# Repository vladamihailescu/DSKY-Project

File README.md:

# DSKY-Project
My open source journey to building a functional, historically-accurate DSKY interface that can be used in simulation. 
 
## v1.0 Hardware (Completed)
 - Raspberry Pi 3B+ running VirtualAGC + driving the display & keyboard
 - Nextion 4.3" LCD HMI (NX4827T043_11) display
 - Alarm Panel PCB designed by Riley Rainey
 - Hand assembled keyboard using Cherry MX blue key switches & Arduino UNO in USB HID mode
 - 3D Printed shell components made from models created/modified by Riley Rainey/Manoel DaSilva from original MIT drawings or myself

## v1.5 Hardware (In Progress)
 - Raspberry Pi 3B+ running VirtualAGC + driving the display & keyboard
 - Nextion 4.3" LCD HMI (NX4827T043_11) display
 - Alarm Panel PCB designed by Riley Rainey
 - Keyboard PCB designed by me with Cherry MX green key switches & LED backlighting
 - 3D Printed shell components made from models created/modified by Riley Rainey/Manoel DaSilva from original MIT drawings or myself

## v2.0 Hardware (Planned)
 - Raspberry Pi 3B+ running VirtualAGC + driving the display & keyboard
 - Custom EL display panel
 - Alarm Panel PCB designed by Riley Rainey
 - Keyboard switches assembled as per original spec using microswitches
 - 3D Printed shell components made from models created/modified by Riley Rainey from original MIT drawings or myself

## Software
 - Drivers for display, alarm panel & keyboard written in Python3
 - VirtualAGC project
 - Project Apollo - NASSP
 
## Setup
Raspberry Pi running VirtualAGC is driving the Nextion HMI, sending lamp instructions to the Alert board and reading keystrokes from Keyboard

## Task List
- 1.0
- [x] Build working GUI for HMI display
- [x] Driver for Nextion HMI display
- [x] Assemble alarm panel PCB
- [x] Driver for alarm panel
- [x] Assemble keyboard
- [x] Driver for keyboard
- [x] Update piDSKY2.py file
- [x] Test with VirtualAGC

- 1.5
- [x] Design & assemble a custom PCB for keyboard
- [ ] Improve code
- [ ] Refine GUI to more closely match original DSKY display
- [ ] Keyboard caps improvements
- [ ] Improve overall DSKY fit & finish & pave way to v2.0

## References
 [VirtualAGC Project](https://www.ibiblio.org/apollo/) - I am so thankful that this exists because it has been my dream to build my own DSKY ever since I first learned of the
 project\
 [Riley Rainey](https://github.com/rrainey) - His amazing work in designing the alert and keyboard PCBs, modeling the DSKY shell and inner components from original drawings gave
 me the opportunity to start this project\
 [Manoel DaSilva](https://github.com/ManoDaSilva) - He created the HMI file which I modified and adapted to my code and the Cherry MX keyswitch stems I used.\

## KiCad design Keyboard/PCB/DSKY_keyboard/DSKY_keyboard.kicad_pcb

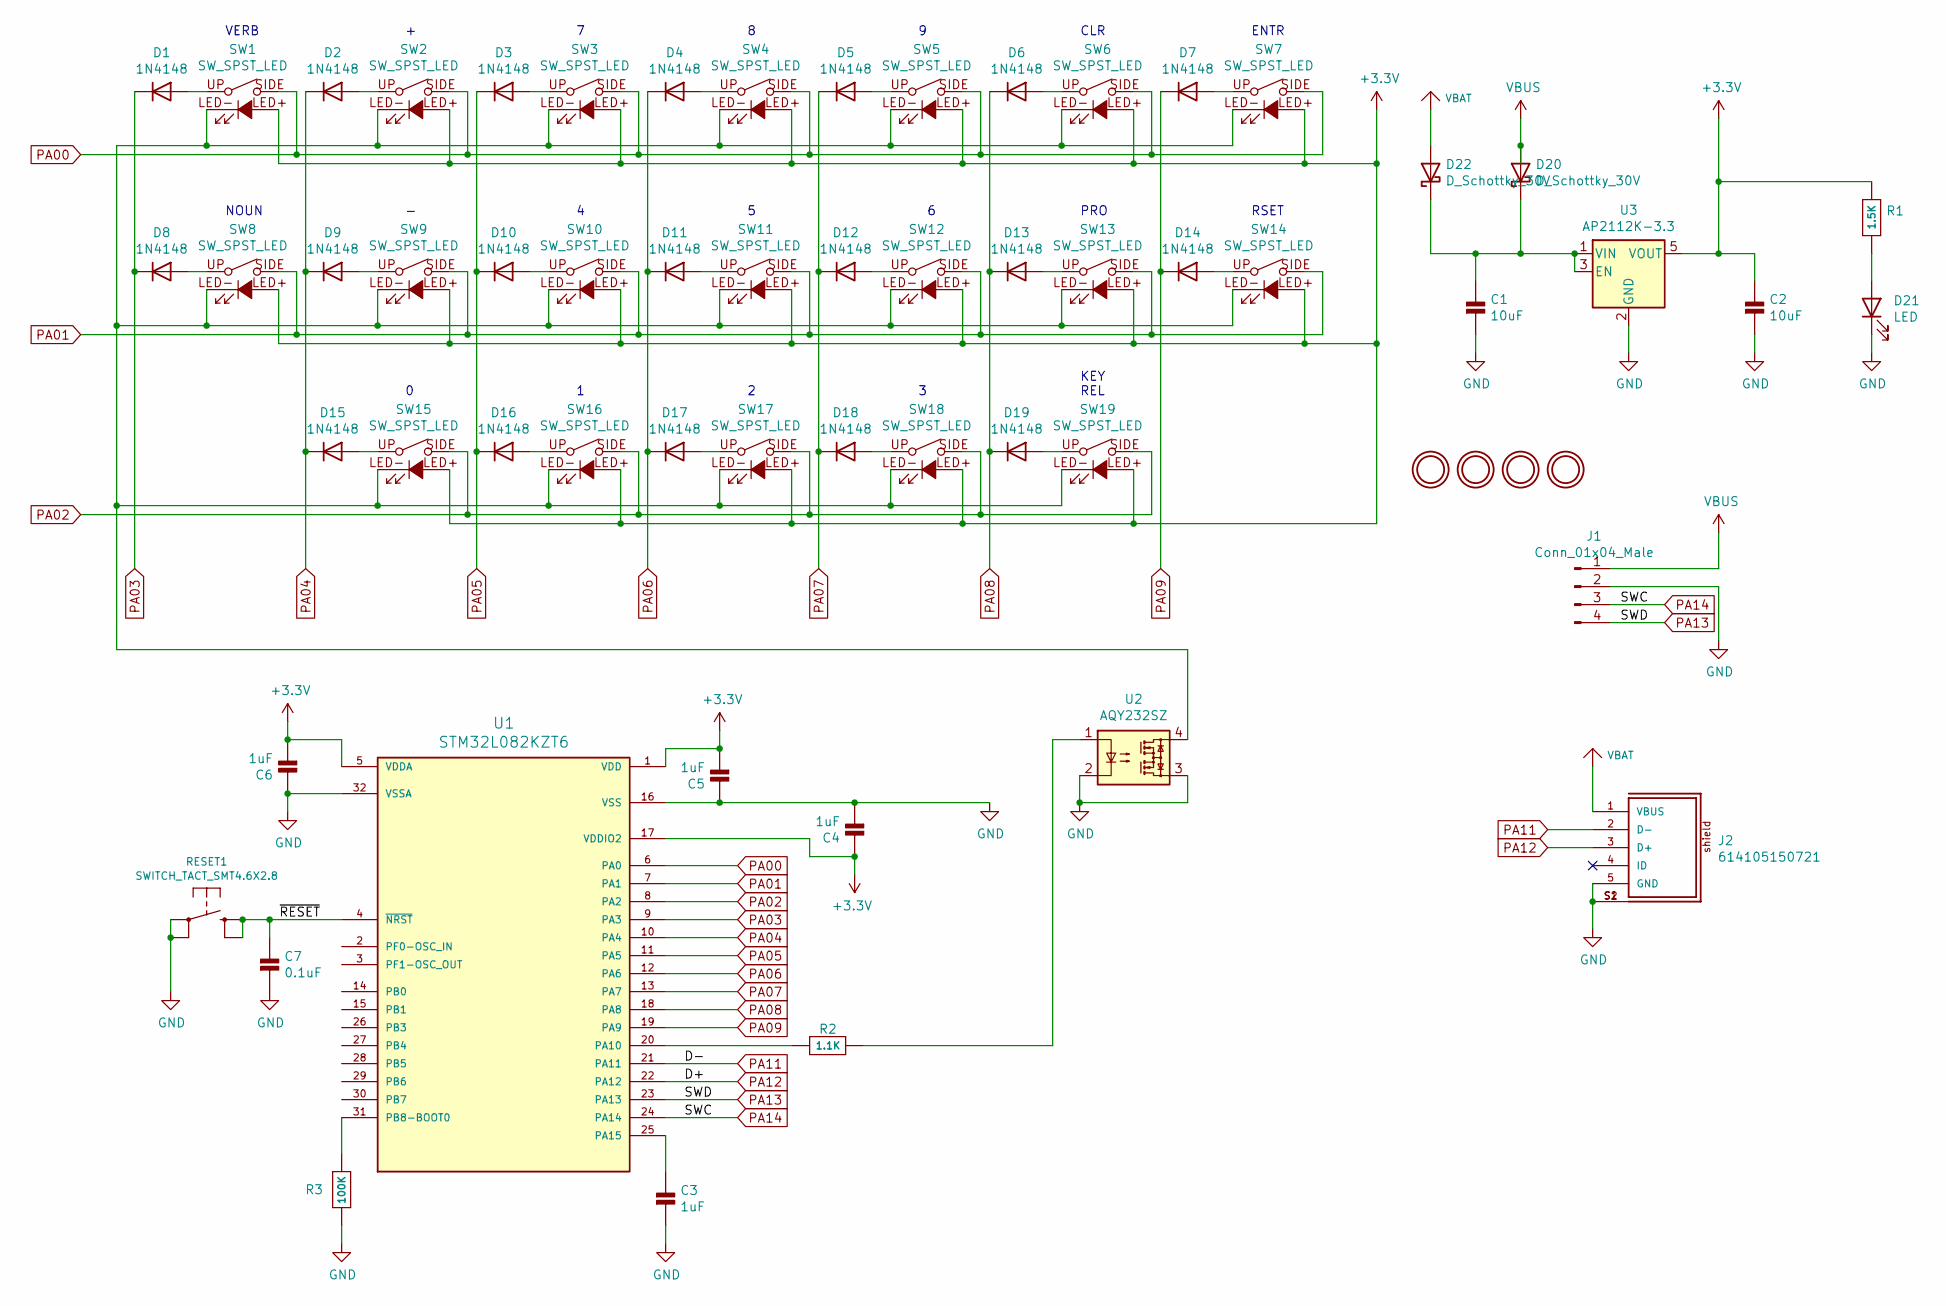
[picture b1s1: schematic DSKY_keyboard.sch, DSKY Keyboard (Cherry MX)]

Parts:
C1, C2: 10uF; 0805-NO
C3, C4, C5, C6: 1uF; 0603-NO
C7: 0.1uF; 0603-NO
D1, D2, D3, D4, D5, D6, D7, D8, D9, D10, D11, D12, D13, D14, D15, D16, D17, D18, D19: 1N4148; SOD-123
D20, D22: D_Schottky_30V; SOD-123FL
D21: LED; CHIPLED_0603_NOOUTLINE
J1: Conn_01x04_Male; PinHeader_1x04_P2.54mm_Horizontal
J2: 614105150721; PART-NUMBER 614105150721
J3, J4, J5, J6: MOUNTINGHOLE3.0; MOUNTINGHOLE_2.0_PLATED
R1: 1.5K; 0603-NO
R2: 1.1K; 0603-NO
R3: 100K; 0603-NO
RESET1: SWITCH_TACT_SMT4.6X2.8; BTN_KMR2_4.6X2.8
SW1, SW2, SW3, SW4, SW5, SW6, SW7, SW8, SW9, SW10, SW11, SW12, SW13, SW14, SW15, SW16, SW17, SW18, SW19: SW_SPST_LED; CHERRYMX-NN-LED
U1: STM32L082KZT6; STM32F042K6T6
U2: AQY232SZ; SO-4_4.4x4.3mm_P2.54mm
U3: AP2112K-3.3; SOT23-5

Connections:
+3V3: C2.1, C4.1, C5.2, C6.2, R1.1, SW1.LED+, SW2.LED+, SW3.LED+, SW4.LED+, SW5.LED+, SW6.LED+, SW7.LED+, SW8.LED+, SW9.LED+, SW10.LED+, SW11.LED+, SW12.LED+, SW13.LED+, SW14.LED+, SW15.LED+, SW16.LED+, SW17.LED+, SW18.LED+, SW19.LED+, U1.1 (VDD), U1.5 (VDDA), U1.17 (VDDIO2), U3.5 (VOUT)
/~RESET: C7.1, RESET1.B (S), RESET1.B' (S1), U1.4 (~NRST)
GND: C1.2, C2.2, C3.2, C4.2, C5.1, C6.1, C7.2, D21.1 (K), J1.2, J2.5 (GND), J2.S1, J2.S2, R3.1, RESET1.A, RESET1.A' (P1), U1.16 (VSS), U1.32 (VSSA), U2.2, U2.3, U3.2 (GND)
unnamed: C1.1, D20.1 (K), D22.1 (K), U3.1 (VIN), U3.3 (EN)
unnamed: C3.1, U1.25 (PA15)
unnamed: D1.2 (A), SW1.UP
unnamed: D2.2 (A), SW2.UP
unnamed: D3.2 (A), SW3.UP
unnamed: D4.2 (A), SW4.UP
unnamed: D5.2 (A), SW5.UP
unnamed: D6.2 (A), SW6.UP
unnamed: D7.2 (A), SW7.UP
unnamed: D8.2 (A), SW8.UP
unnamed: D9.2 (A), SW9.UP
unnamed: D10.2 (A), SW10.UP
unnamed: D11.2 (A), SW11.UP
unnamed: D12.2 (A), SW12.UP
unnamed: D13.2 (A), SW13.UP
unnamed: D14.2 (A), SW14.UP
unnamed: D15.2 (A), SW15.UP
unnamed: D16.2 (A), SW16.UP
unnamed: D17.2 (A), SW17.UP
unnamed: D18.2 (A), SW18.UP
unnamed: D19.2 (A), SW19.UP
unnamed: D21.2 (A), R1.2
unnamed: R2.1, U2.1
unnamed: R2.2, U1.20 (PA10)
unnamed: R3.2, U1.31 (PB8-BOOT0)
unnamed: SW1.LED-, SW2.LED-, SW3.LED-, SW4.LED-, SW5.LED-, SW6.LED-, SW7.LED-, SW8.LED-, SW9.LED-, SW10.LED-, SW11.LED-, SW12.LED-, SW13.LED-, SW14.LED-, SW15.LED-, SW16.LED-, SW17.LED-, SW18.LED-, SW19.LED-, U2.4
PA00: SW1.SIDE, SW2.SIDE, SW3.SIDE, SW4.SIDE, SW5.SIDE, SW6.SIDE, SW7.SIDE, U1.6 (PA0)
PA01: SW8.SIDE, SW9.SIDE, SW10.SIDE, SW11.SIDE, SW12.SIDE, SW13.SIDE, SW14.SIDE, U1.7 (PA1)
PA02: SW15.SIDE, SW16.SIDE, SW17.SIDE, SW18.SIDE, SW19.SIDE, U1.8 (PA2)
PA03: D1.1 (K), D8.1 (K), U1.9 (PA3)
PA04: D2.1 (K), D9.1 (K), D15.1 (K), U1.10 (PA4)
PA05: D3.1 (K), D10.1 (K), D16.1 (K), U1.11 (PA5)
PA06: D4.1 (K), D11.1 (K), D17.1 (K), U1.12 (PA6)
PA07: D5.1 (K), D12.1 (K), D18.1 (K), U1.13 (PA7)
PA08: D6.1 (K), D13.1 (K), D19.1 (K), U1.18 (PA8)
PA09: D7.1 (K), D14.1 (K), U1.19 (PA9)
PA11: J2.2 (D-), U1.21 (PA11)
PA12: J2.3 (D+), U1.22 (PA12)
PA13: J1.4, U1.23 (PA13)
PA14: J1.3, U1.24 (PA14)
VBAT: D22.2 (A), J2.1 (VBUS)
VBUS: D20.2 (A), J1.1

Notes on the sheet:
RSET
CLR
ENTR
KEY REL
PRO
NOUN
VERB

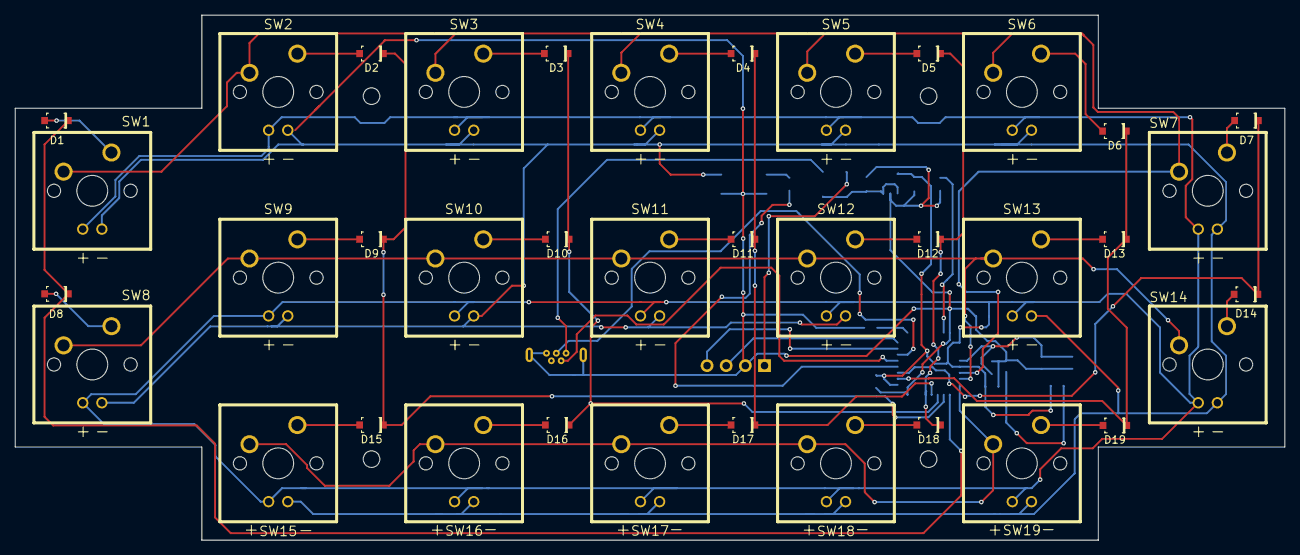
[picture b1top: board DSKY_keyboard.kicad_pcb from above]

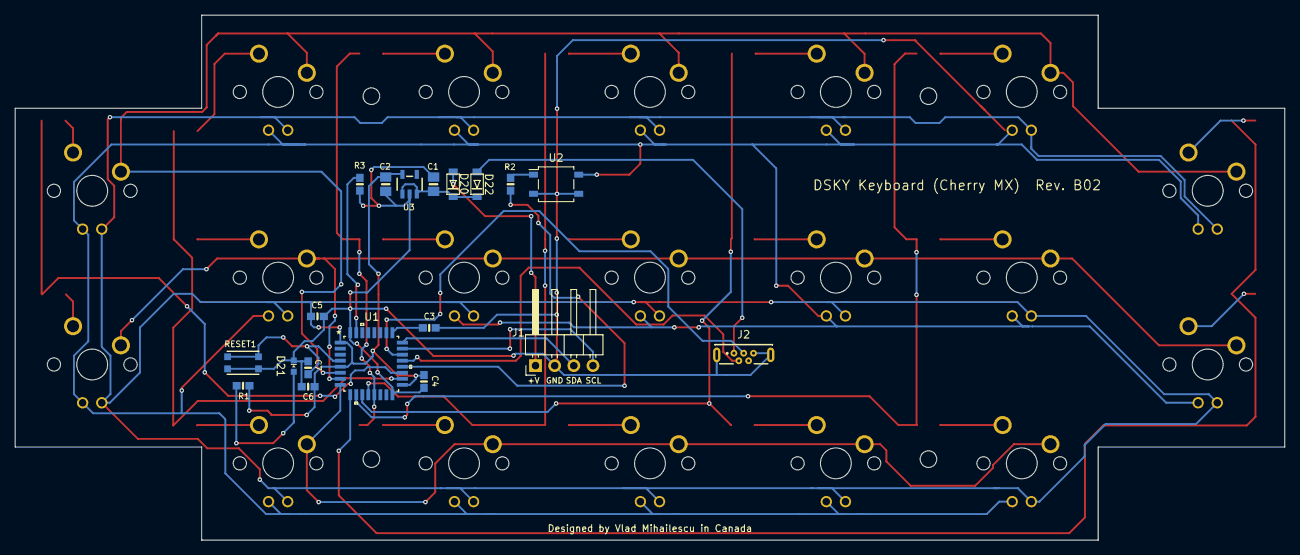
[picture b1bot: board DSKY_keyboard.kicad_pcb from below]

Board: 2 copper layers, 168.4 x 69.6 mm, 57 parts (19 on the bottom side), 45 nets.

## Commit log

2021-02-04 LICENSE
2021-02-20 Added new/updated files
2021-03-20 Added keyboard PCB files
2021-03-20 Updated PCB
2021-03-23 PCB updates

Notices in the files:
Keyboard/PCB/DSKY_keyboard/DSKY_keyboard.kicad_pcb:
License: CC BY 4.0
Keyboard/PCB/DSKY_keyboard/DSKY_keyboard.sch:
creativecommons.org/licenses/by/4.0
parts and their libraries:
Copyright 2016 Accelerated Designs. All rights reserved.
